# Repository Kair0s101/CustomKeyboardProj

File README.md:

# CustomKeyboardProj
Custom BT/Wired ground up keyboard build

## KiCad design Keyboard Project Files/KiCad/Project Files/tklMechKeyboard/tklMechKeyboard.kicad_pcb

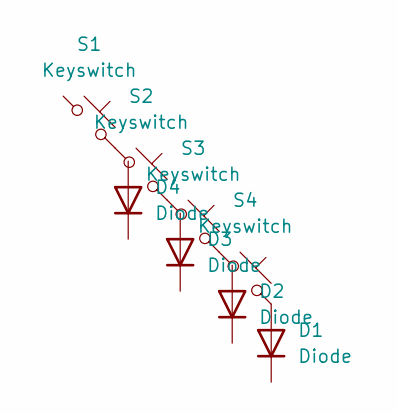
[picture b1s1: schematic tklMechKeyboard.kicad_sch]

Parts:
D1, D2, D3, D4: Diode; Diode_DO-35
S1, S2, S3, S4: Keyswitch; MX_PCB_1.00u

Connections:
unnamed: D1.2 (A), S4.2
unnamed: S1.2, S2.1
unnamed: S2.2, S3.1
unnamed: S3.2, S4.1

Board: 2 copper layers, 8 parts (4 on the bottom side), 4 nets, no tracks yet.

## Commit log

2024-07-26 Inital Commit
    Initial commit of struct
2024-07-26 Added Submodules
2024-07-26 Added Lib to Kicad
2024-07-26 Reinstall Kicad - resolved issue hopefully re 3d models
